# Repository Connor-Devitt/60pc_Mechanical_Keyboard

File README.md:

# 60pc_Mechanical_Keyboard
60% size mechanical keyboard design including PCB, frame, firmware. 

## The PCB (kiCAD)
* PCB uses a 60% keyboard layout
* Footprints for Cherry MX and clones.
* Microcontroller is ATmega32u4.
* Interfaces to PC over USB micro.

## The Frame (Inventor 2018)
* Made out of sheet aluminum
* Cutouts for cherry style stabilizers
* Approximatly 5 degree slope

## Versions
Version 1.0: Initial release
Version 1.1: Smaller form factor and improved differential routing

## Pictures (v1.0)

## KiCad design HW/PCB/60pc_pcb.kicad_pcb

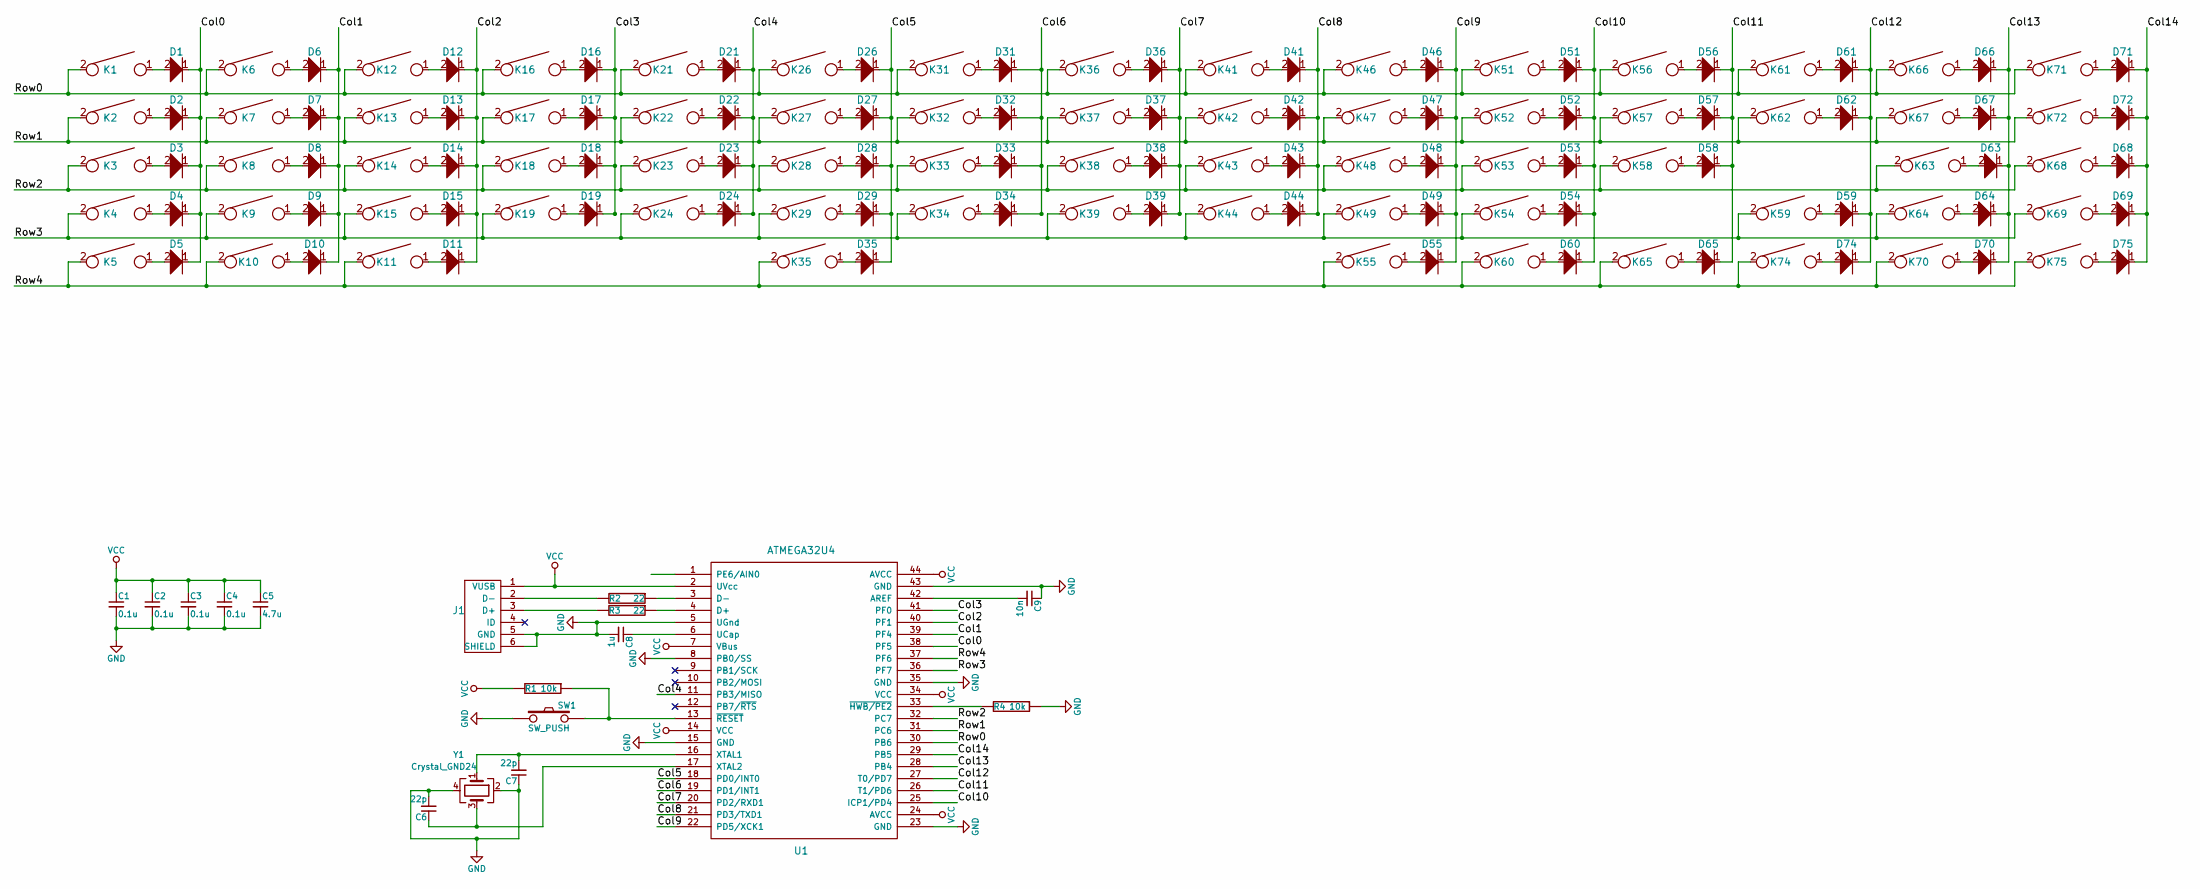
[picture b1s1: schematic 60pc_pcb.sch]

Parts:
C1, C2, C3, C4: 0.1u; C_0805_HandSoldering
C5: 4.7u; C_0805_HandSoldering
C6, C7: 22p; C_0805_HandSoldering
C8: 1u; C_0805_HandSoldering
C9: 10n; C_0805_HandSoldering
D1, D2, D3, D4, D5, D6, D7, D8, D9, D10, D11, D12, D13, D14, D15, D16, D17, D18, D19, D21, D22, D23, D24, D26, D27, D28, D29, D31, D32, D33, D34, D35, D36, D37, D38, D39, D41, D42, D43, D44, D46, D47, D48, D49, D51, D52, D53, D54, D55, D56, D57, D58, D59, D60, D61, D62, D63, D64, D65, D66, D67, D68, D69, D70, D71, D72, D74, D75: D; D_SOD123_axial
J1: USB_mini_micro_B; USB_miniB_hirose_5S8
K1, K6, K7, K8, K9, K12, K13, K14, K15, K16, K17, K18, K19, K21, K22, K23, K24, K26, K27, K28, K29, K31, K32, K33, K34, K36, K37, K38, K39, K41, K42, K43, K44, K46, K47, K48, K49, K51, K52, K53, K54, K55, K56, K57, K58, K60, K61, K62, K64, K65, K68, K69, K70, K71, K72, K74, K75: KEYSW; Mx_Alps_100
K2, K67: KEYSW; Mx_Alps_150
K3, K59: KEYSW; Mx_Alps_175
K4, K63: KEYSW; Mx_Alps_225
K5, K10, K11: KEYSW; Mx_Alps_125
K35: KEYSW; Mx_Alps_625
K66: KEYSW; Mx_Alps_200
R1, R4: 10k; R_0805_HandSoldering
R2, R3: 22; R_0805_HandSoldering
SW1: SW_PUSH; SW_SPST_TL3342
U1: ATMEGA32U4; TQFP-44_10x10mm_Pitch0.8mm
Y1: Crystal_GND24; Crystal_SMD_SeikoEpson_TSX3225-4pin_3.2x2.5mm_HandSoldering

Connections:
/Col0: D1.1, D2.1, D3.1, D4.1, D5.1, U1.38 (PF5)
/Col1: D6.1, D7.1, D8.1, D9.1, D10.1, U1.39 (PF4)
/Col2: D11.1, D12.1, D13.1, D14.1, D15.1, U1.40 (PF1)
/Col3: D16.1, D17.1, D18.1, D19.1, U1.41 (PF0)
/Col4: D21.1, D22.1, D23.1, D24.1, U1.11 (PB3/MISO)
/Col5: D26.1, D27.1, D28.1, D29.1, D35.1, U1.18 (PD0/INT0)
/Col6: D31.1, D32.1, D33.1, D34.1, U1.19 (PD1/INT1)
/Col7: D36.1, D37.1, D38.1, D39.1, U1.20 (PD2/RXD1)
/Col8: D41.1, D42.1, D43.1, D44.1, U1.21 (PD3/TXD1)
/Col9: D46.1, D47.1, D48.1, D49.1, D55.1, U1.22 (PD5/XCK1)
/Col10: D51.1, D52.1, D53.1, D54.1, D60.1, U1.25 (ICP1/PD4)
/Col11: D56.1, D57.1, D58.1, D65.1, U1.26 (T1/PD6)
/Col12: D59.1, D61.1, D62.1, D74.1, U1.27 (T0/PD7)
/Col13: D63.1, D64.1, D66.1, D67.1, D70.1, U1.28 (PB4)
/Col14: D68.1, D69.1, D71.1, D72.1, D75.1, U1.29 (PB5)
/Row0: K1.2, K6.2, K12.2, K16.2, K21.2, K26.2, K31.2, K36.2, K41.2, K46.2, K51.2, K56.2, K61.2, K66.2, K71.2, U1.30 (PB6)
/Row1: K2.2, K7.2, K13.2, K17.2, K22.2, K27.2, K32.2, K37.2, K42.2, K47.2, K52.2, K57.2, K62.2, K67.2, K72.2, U1.31 (PC6)
/Row2: K3.2, K8.2, K14.2, K18.2, K23.2, K28.2, K33.2, K38.2, K43.2, K48.2, K53.2, K58.2, K63.2, K68.2, U1.32 (PC7)
/Row3: K4.2, K9.2, K15.2, K19.2, K24.2, K29.2, K34.2, K39.2, K44.2, K49.2, K54.2, K59.2, K64.2, K69.2, U1.36 (PF7)
/Row4: K5.2, K10.2, K11.2, K35.2, K55.2, K60.2, K65.2, K70.2, K74.2, K75.2, U1.37 (PF6)
GND: C1.2, C2.2, C3.2, C4.2, C5.2, C6.2, C7.1, C8.2, C9.1, J1.5 (GND), J1.6 (SHIELD), R4.1, SW1.1, U1.5 (UGnd), U1.8 (PB0/SS), U1.15 (GND), U1.23 (GND), U1.35 (GND), U1.43 (GND), Y1.2, Y1.4
unnamed: C6.1, U1.17 (XTAL2), Y1.3
unnamed: C7.2, U1.16 (XTAL1), Y1.1
unnamed: C8.1, U1.6 (UCap)
unnamed: C9.2, U1.42 (AREF)
unnamed: D1.2, K1.1
unnamed: D2.2, K2.1
unnamed: D3.2, K3.1
unnamed: D4.2, K4.1
unnamed: D5.2, K5.1
unnamed: D6.2, K6.1
unnamed: D7.2, K7.1
unnamed: D8.2, K8.1
unnamed: D9.2, K9.1
unnamed: D10.2, K10.1
unnamed: D11.2, K11.1
unnamed: D12.2, K12.1
unnamed: D13.2, K13.1
unnamed: D14.2, K14.1
unnamed: D15.2, K15.1
unnamed: D16.2, K16.1
unnamed: D17.2, K17.1
unnamed: D18.2, K18.1
unnamed: D19.2, K19.1
unnamed: D21.2, K21.1
unnamed: D22.2, K22.1
unnamed: D23.2, K23.1
unnamed: D24.2, K24.1
unnamed: D26.2, K26.1
unnamed: D27.2, K27.1
unnamed: D28.2, K28.1
unnamed: D29.2, K29.1
unnamed: D31.2, K31.1
unnamed: D32.2, K32.1
unnamed: D33.2, K33.1
unnamed: D34.2, K34.1
unnamed: D35.2, K35.1
unnamed: D36.2, K36.1
unnamed: D37.2, K37.1
unnamed: D38.2, K38.1
unnamed: D39.2, K39.1
unnamed: D41.2, K41.1
unnamed: D42.2, K42.1
unnamed: D43.2, K43.1
unnamed: D44.2, K44.1
unnamed: D46.2, K46.1
unnamed: D47.2, K47.1
unnamed: D48.2, K48.1
unnamed: D49.2, K49.1
unnamed: D51.2, K51.1
unnamed: D52.2, K52.1
unnamed: D53.2, K53.1
unnamed: D54.2, K54.1
unnamed: D55.2, K55.1
unnamed: D56.2, K56.1
unnamed: D57.2, K57.1
unnamed: D58.2, K58.1
unnamed: D59.2, K59.1
unnamed: D60.2, K60.1
unnamed: D61.2, K61.1
unnamed: D62.2, K62.1
unnamed: D63.2, K63.1
unnamed: D64.2, K64.1
unnamed: D65.2, K65.1
unnamed: D66.2, K66.1
unnamed: D67.2, K67.1
unnamed: D68.2, K68.1
unnamed: D69.2, K69.1
unnamed: D70.2, K70.1
unnamed: D71.2, K71.1
unnamed: D72.2, K72.1
unnamed: D74.2, K74.1
unnamed: D75.2, K75.1
unnamed: J1.2 (D-), R2.2
unnamed: J1.3 (D+), R3.2
unnamed: R1.1, SW1.2, U1.13 (~RESET)
unnamed: R2.1, U1.3 (D-)
unnamed: R3.1, U1.4 (D+)
unnamed: R4.2, U1.33 (~HWB/PE2)
VCC: C1.1, C2.1, C3.1, C4.1, C5.1, J1.1 (VUSB), R1.2, U1.2 (UVcc), U1.7 (VBus), U1.14 (VCC), U1.24 (AVCC), U1.34 (VCC), U1.44 (AVCC)

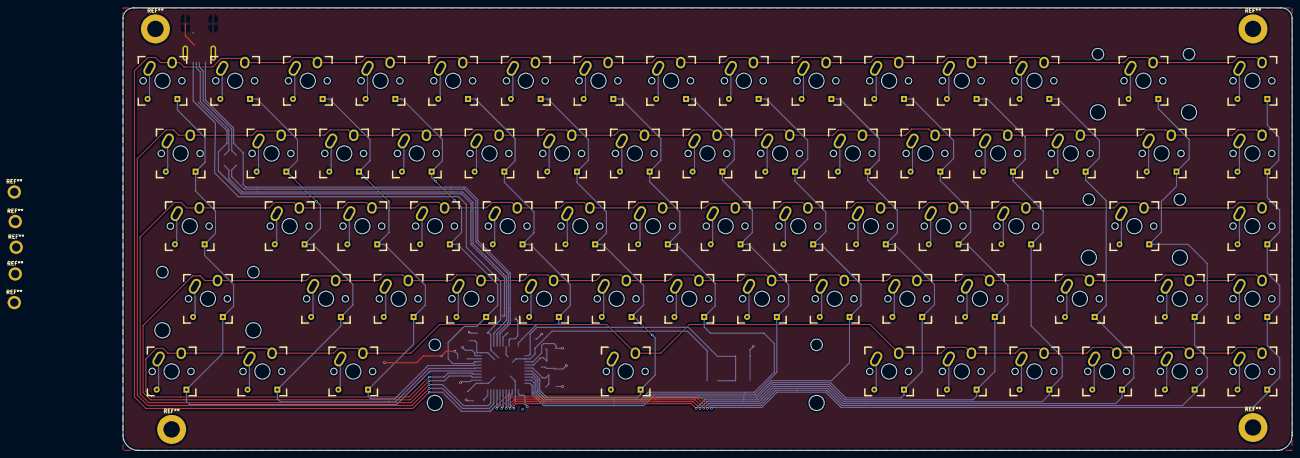
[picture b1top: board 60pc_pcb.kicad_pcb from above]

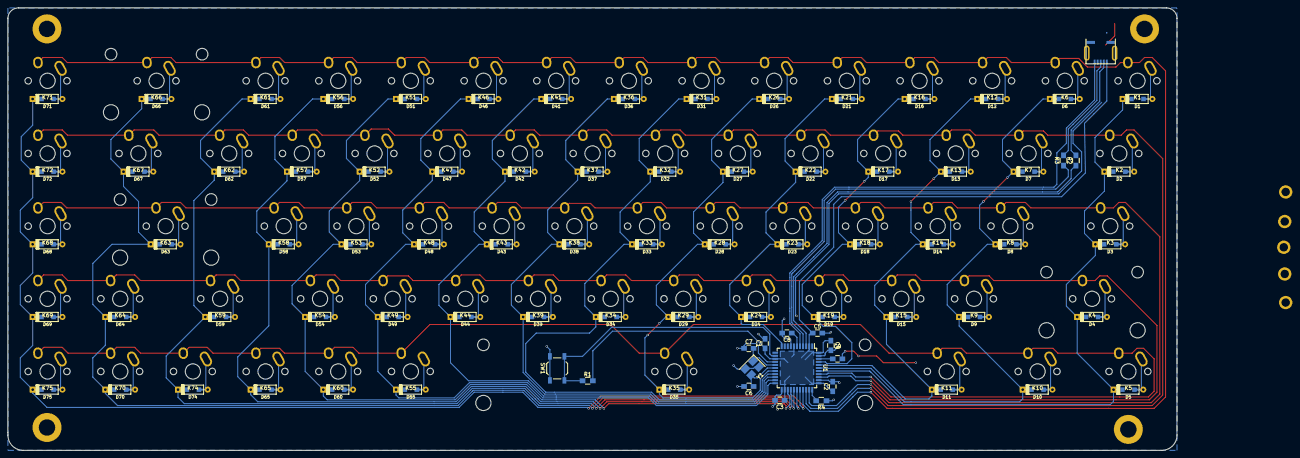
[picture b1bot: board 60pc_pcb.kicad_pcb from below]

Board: 2 copper layers, 306.5 x 116.0 mm, 153 parts (85 on the bottom side), 100 nets.

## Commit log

2018-02-01 init
2018-02-01 Formatting lul
2018-02-01 Formatting lul x2
2018-02-01 Inventor project setup
2018-02-04 Added M4 mounting holes to pcb
2018-02-05 3D updates
    New 3d pcb and frame top outline
2018-02-05 Added frame cutouts
2018-02-08 Frame part near compeltion
2018-02-08 details
2018-02-10 Frame and Assembly finished
2018-02-10 Added some renderings
2018-02-10 Added some stuff
2018-02-10 Reorganized
2018-02-10 Added pictures
2018-02-10 Formatting
2018-02-10 Format
2018-02-17 Version 1.1 edits
    Smaller form factor.
    4x M4 screws to 5x M2 screws.
    Screws now placed between switched.
    Dufferential routing return path and impedance matching improved.
2018-02-17 Update to include versions
2018-02-25 Added Usb hole to v1.1
2018-02-25 Preparations for CNC
2018-03-23 Finished up hardware changes, setup SW project
2018-04-29 Added hex
2018-04-29 removed a hex
2018-06-29 finished build picture
